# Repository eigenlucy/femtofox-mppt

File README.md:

# femtofox-mppt

MPPT/BMS hat for the FemtoFox Linux Meshtastic Node: https://github.com/noon92/femtofox

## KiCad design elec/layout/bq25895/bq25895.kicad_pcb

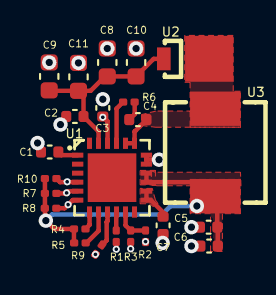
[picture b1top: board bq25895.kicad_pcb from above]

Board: 4 copper layers, 24 parts (0 on the bottom side), 17 nets.

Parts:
C1: 25V 1uF X5R ±10% 0402 Multilayer Ceramic Capacito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; C0402
C2, C5, C6, C7: 6.3V 10uF X5R ±20% 0402 Multilayer Ceramic Capaci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; C0402
C3: 10V 4.7uF X5R ±20% 0402 Multilayer Ceramic Capaci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; C0402
C4: 50V 47nF X7R ±10% 0402 Multilayer Ceramic Capacit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; C0402
C8: 6.3V 22uF X5R ±20% 0603 Multilayer Ceramic Capaci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; C0603
C9, C10, C11: 10V 10uF X5R ±10% 0603 Multilayer Ceramic Capacit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; C0603
R1: 50mW Thick Film Resistors ±1% ±200ppm/℃ 127Ω 0201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; R0201
R2: 50mW Thick Film Resistors 25V ±1% ±200ppm/℃ 5.1kΩ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; R0201
R3: 50mW Thick Film Resistors 25V ±5% ±200ppm/℃ 30kΩ 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; R0201
R4, R5, R7, R8, R9, R10: 50mW Thick Film Resistors 25V ±1% ±200ppm/℃ 10kΩ 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; R0201
R6: 50mW Thick Film Resistors 25V ±1% 0Ω 0201 Chip Re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; R0201
U1: ?; QFN-24_L4.0-W4.0-P0.50-TL-EP2.7
U2: ?; DO-220AA_L3.4-W2.0-LS3.9-RD
U3: ?; IND-SMD_L5.2-W5.2_IHLP2020CZER2R2M11

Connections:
C4-vcc: C4.1, R6.2
btst: R6.1, U1.21
ce: R9.1, U1.9
gnd: C1.2, C2.2, C3.2, C5.2, C6.2, C7.2, C8.2, C9.2, C10.2, C11.2, R1.2, R3.2, R9.2, U1.17, U1.18, U1.25
ilim: R1.1, U1.10
int: R4.1, U1.7
otg: R5.1, U1.8
regn: C3.1, R2.1, U1.22
scl: R7.1, U1.5
sda: R8.1, U1.6
stat: R10.1, U1.4
sw: C4.2, U1.19, U1.20, U2.1, U3.1
ts: R2.2, R3.1, U1.11
vcc-1: C1.1, U1.1
vcc-2: C7.1, U1.13, U1.14
vcc-3: C5.1, C6.1, R4.2, R5.2, R7.2, R8.2, R10.2, U1.15, U1.16, U3.2
vcc-5: C2.1, C8.1, C9.1, C10.1, C11.1, U1.23, U2.2

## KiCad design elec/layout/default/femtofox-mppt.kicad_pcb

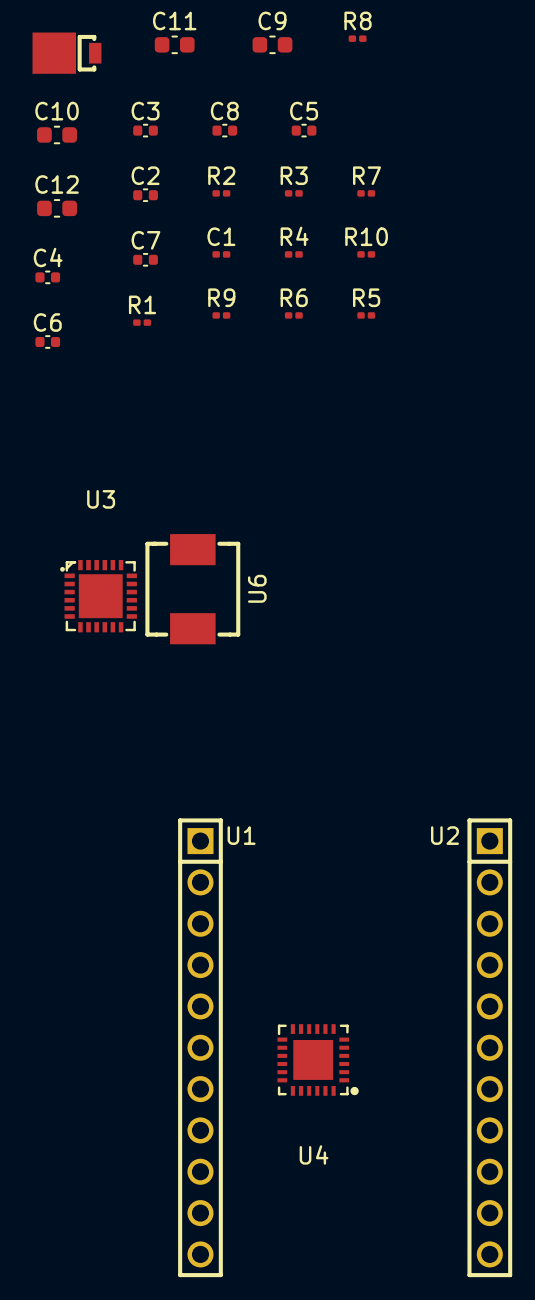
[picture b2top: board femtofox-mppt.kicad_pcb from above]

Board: 2 copper layers, 28 parts (0 on the bottom side), 18 nets, no tracks yet.

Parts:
C1: 10V 100nF X5R ±10% 0201 Multilayer Ceramic Capaci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; C0201
C2: 25V 1uF X5R ±10% 0402 Multilayer Ceramic Capacito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; C0402
C3, C6, C7, C8: 6.3V 10uF X5R ±20% 0402 Multilayer Ceramic Capaci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; C0402
C4: 10V 4.7uF X5R ±20% 0402 Multilayer Ceramic Capaci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; C0402
C5: 50V 47nF X7R ±10% 0402 Multilayer Ceramic Capacit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; C0402
C9: 6.3V 22uF X5R ±20% 0603 Multilayer Ceramic Capaci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; C0603
C10, C11, C12: 10V 10uF X5R ±10% 0603 Multilayer Ceramic Capacit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; C0603
R1: 50mW Thick Film Resistors 25V ±1% ±200ppm/℃ 120Ω 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; R0201
R2: 50mW Thick Film Resistors 25V ±1% ±200ppm/℃ 5.1kΩ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; R0201
R3: 50mW Thick Film Resistors 25V ±5% ±200ppm/℃ 30kΩ 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; R0201
R4, R5, R7, R8, R9, R10: 50mW Thick Film Resistors 25V ±1% ±200ppm/℃ 10kΩ 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; R0201
R6: 50mW Thick Film Resistors 25V ±5% 0Ω 0201 Chip Re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; R0201
U1, U2: ?; HDR-TH_11P-P2.54-V-M
U3: ?; QFN-24_L4.0-W4.0-P0.50-TL-EP2.7
U4: ?; VQFN-24_L4.0-W4.0-P0.50-TL-EP2.5
U5: ?; DO-220AA_L3.4-W2.0-LS3.9-RD
U6: ?; IND-SMD_L5.2-W5.2_IHLP2020CZER2R2M11

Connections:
C4-vcc: C5.1, R6.2
btst: R6.1, U3.21
ce: R9.1, U3.9
femtohat.row1-gnd: U1.2, U2.2
gnd: C1.2, C2.2, C3.2, C4.2, C6.2, C7.2, C8.2, C9.2, C10.2, C11.2, C12.2, R1.2, R3.2, R9.2, U3.17, U3.18
ic-scl: R7.1, U3.5, U4.16
ic-sda: R8.1, U3.6, U4.15
ilim: R1.1, U3.10
int: R4.1, U3.7
otg: R5.1, U3.8
regn: C4.1, R2.1, U3.22
stat: R10.1, U3.4
sw: C5.2, U3.19, U3.20, U5.1, U6.1
ts: R2.2, R3.1, U3.11
vcc-1: C2.1, U3.1
vcc-2: C8.1, U3.13, U3.14
vcc-3: C1.1, C6.1, C7.1, R4.2, R5.2, R7.2, R8.2, R10.2, U3.15, U3.16, U4.4, U6.2
vcc-5: C3.1, C9.1, C10.1, C11.1, C12.1, U3.23, U5.2

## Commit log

2024-12-10 Configure project
2024-12-10 added refs
2024-12-10 changed refs
2024-12-10 changed readme
2024-12-13 edits
2024-12-13 built with usb sw edits, eod
2024-12-19 checkpoint
2024-12-19 eod 12/19/24
2025-01-13 rebuilt, some layout changes
